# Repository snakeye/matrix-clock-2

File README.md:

# LED Matrix Clock

These clock are build using ESP8266 module ESP-12. Arduino IDE was used for the firmware development and upload.

## Features

* Built on ESP8266 WiFi module
* Time updates via NTP protocol
* Automatic time zone support
* Timekeeping without Internet connection (DS3231 chip)
* Brightness auto adjust

## Dependencies

* WiFi Manager - [https://github.com/tzapu/WiFiManager](https://github.com/tzapu/WiFiManager)
* Time library - [https://github.com/PaulStoffregen/Time](https://github.com/PaulStoffregen/Time)
* Time zone library - [https://github.com/JChristensen/Timezone](https://github.com/JChristensen/Timezone)
* NTP Client - [https://github.com/gmag11/NtpClient](https://github.com/gmag11/NtpClient)
* RTC library - [https://github.com/Makuna/Rtc](https://github.com/Makuna/Rtc)
* MAX7219 library - [https://github.com/snakeye/MAX7219_Display](https://github.com/snakeye/MAX7219_Display)

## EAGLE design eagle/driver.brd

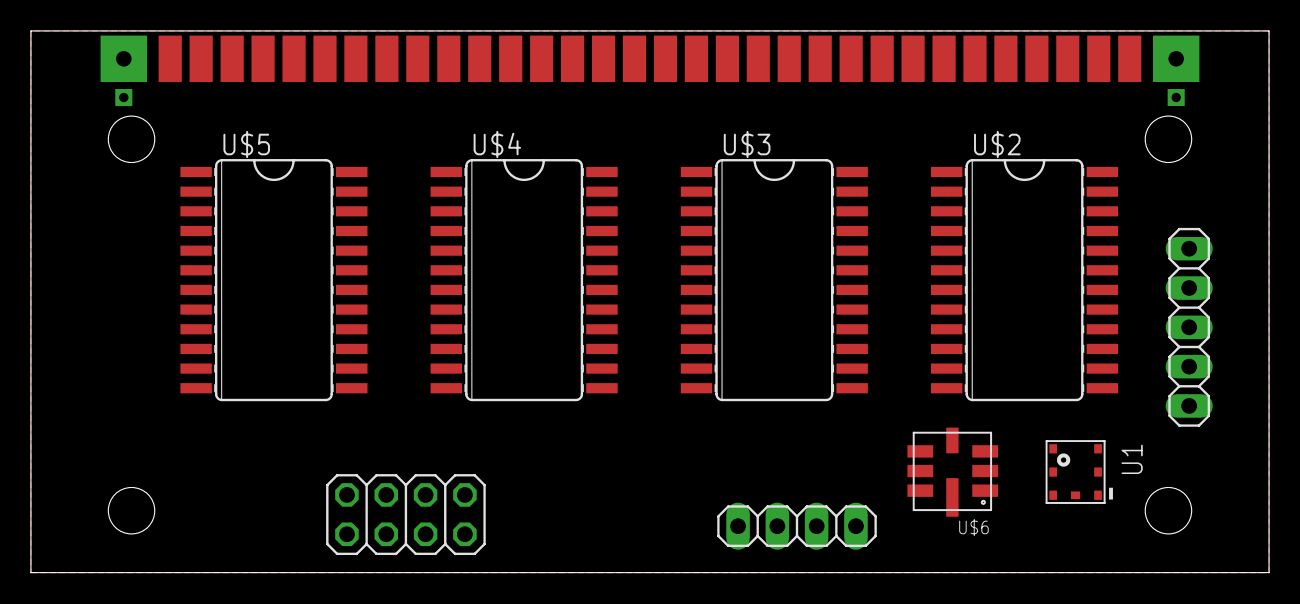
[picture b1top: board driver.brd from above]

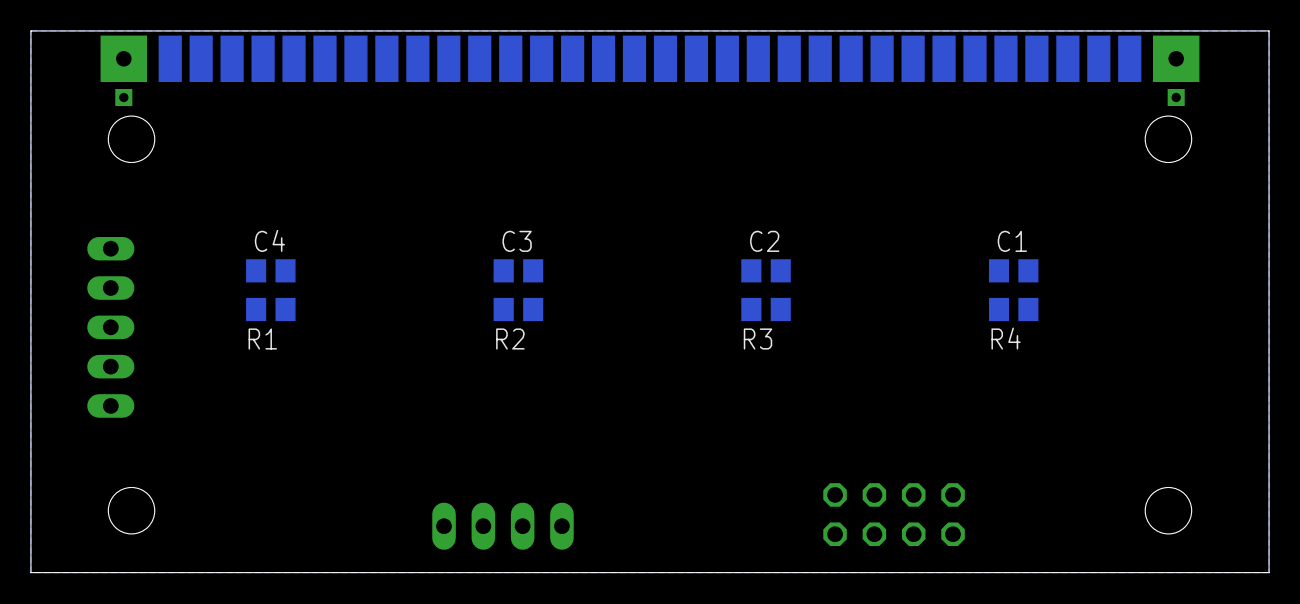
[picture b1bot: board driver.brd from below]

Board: 2 copper layers, 80.0 x 35.0 mm, 18 parts (8 on the bottom side), 79 nets, no tracks yet.

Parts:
C1, C2, C3, C4: C0805
JP1: PROG; 2X04
JP2: DISPLAY; 1X05
JP3: I2C; 1X04
R1, R2, R3, R4: R0805
U1: BMP180
U$1: ANGLE_BOARD_CONNECTORTWO_SIDED; TWO_SIDED
U$2, U$3, U$4, U$5: MAX7219CWG; SO24L
U$6: BMP085

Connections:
+3V3: JP1.7, JP3.3, U1.2, U1.3, U$6.3, U$6.4
+5V: C1.1, C2.1, C3.1, C4.1, JP2.5, R1.1, R2.1, R3.1, R4.1, U$2.19, U$3.19, U$4.19, U$5.19
DSP_CLK: JP2.2, U$2.13, U$3.13, U$4.13, U$5.13
DSP_CS: JP2.3, U$2.12, U$3.12, U$4.12, U$5.12
DSP_DIN: JP2.1, U$2.1
GND: C1.2, C2.2, C3.2, C4.2, JP1.2, JP2.4, JP3.4, U1.7, U$1.GND@1, U$1.GND@2, U$1.GND@3, U$1.GND@4, U$2.4, U$2.9, U$3.4, U$3.9, U$4.4, U$4.9, U$5.4, U$5.9, U$6.1
M1C1: U$1.P$64, U$2.2
M1C2: U$1.P$63, U$2.11
M1C3: U$1.P$62, U$2.6
M1C4: U$1.P$61, U$2.7
M1C5: U$1.P$60, U$2.3
M1C6: U$1.P$59, U$2.10
M1C7: U$1.P$58, U$2.5
M1C8: U$1.P$57, U$2.8
M1R1: U$1.P$1, U$2.14
M1R2: U$1.P$2, U$2.16
M1R3: U$1.P$3, U$2.20
M1R4: U$1.P$4, U$2.23
M1R5: U$1.P$5, U$2.21
M1R6: U$1.P$6, U$2.15
M1R7: U$1.P$7, U$2.17
M1R8: U$1.P$8, U$2.22
M2C1: U$1.P$56, U$3.2
M2C2: U$1.P$55, U$3.11
M2C3: U$1.P$54, U$3.6
M2C4: U$1.P$53, U$3.7
M2C5: U$1.P$52, U$3.3
M2C6: U$1.P$51, U$3.10
M2C7: U$1.P$50, U$3.5
M2C8: U$1.P$49, U$3.8
M2R1: U$1.P$9, U$3.14
M2R2: U$1.P$10, U$3.16
M2R3: U$1.P$11, U$3.20
M2R4: U$1.P$12, U$3.23
M2R5: U$1.P$13, U$3.21
M2R6: U$1.P$14, U$3.15
M2R7: U$1.P$15, U$3.17
M2R8: U$1.P$16, U$3.22
M3C1: U$1.P$48, U$4.2
M3C2: U$1.P$47, U$4.11
M3C3: U$1.P$46, U$4.6
M3C4: U$1.P$45, U$4.7
M3C5: U$1.P$44, U$4.3
M3C6: U$1.P$43, U$4.10
M3C7: U$1.P$42, U$4.5
M3C8: U$1.P$41, U$4.8
M3R1: U$1.P$17, U$4.14
M3R2: U$1.P$18, U$4.16
M3R3: U$1.P$19, U$4.20
M3R4: U$1.P$20, U$4.23
M3R5: U$1.P$21, U$4.21
M3R6: U$1.P$22, U$4.15
M3R7: U$1.P$23, U$4.17
M3R8: U$1.P$24, U$4.22
M4C1: U$1.P$40, U$5.2
M4C2: U$1.P$39, U$5.11
M4C3: U$1.P$38, U$5.6
M4C4: U$1.P$37, U$5.7
M4C5: U$1.P$36, U$5.3
M4C6: U$1.P$35, U$5.10
M4C7: U$1.P$34, U$5.5
M4C8: U$1.P$33, U$5.8
M4R1: U$1.P$25, U$5.14
M4R2: U$1.P$26, U$5.16
M4R3: U$1.P$27, U$5.20
M4R4: U$1.P$28, U$5.23
M4R5: U$1.P$29, U$5.21
M4R6: U$1.P$30, U$5.15
M4R7: U$1.P$31, U$5.17
M4R8: U$1.P$32, U$5.22
unnamed: R1.2, U$2.18
unnamed: U$2.24, U$3.1
unnamed: R2.2, U$3.18
unnamed: U$3.24, U$4.1
unnamed: R3.2, U$4.18
unnamed: U$4.24, U$5.1
unnamed: R4.2, U$5.18
SCL: JP3.1, U1.5, U$6.6
SDA: JP3.2, U1.6, U$6.7

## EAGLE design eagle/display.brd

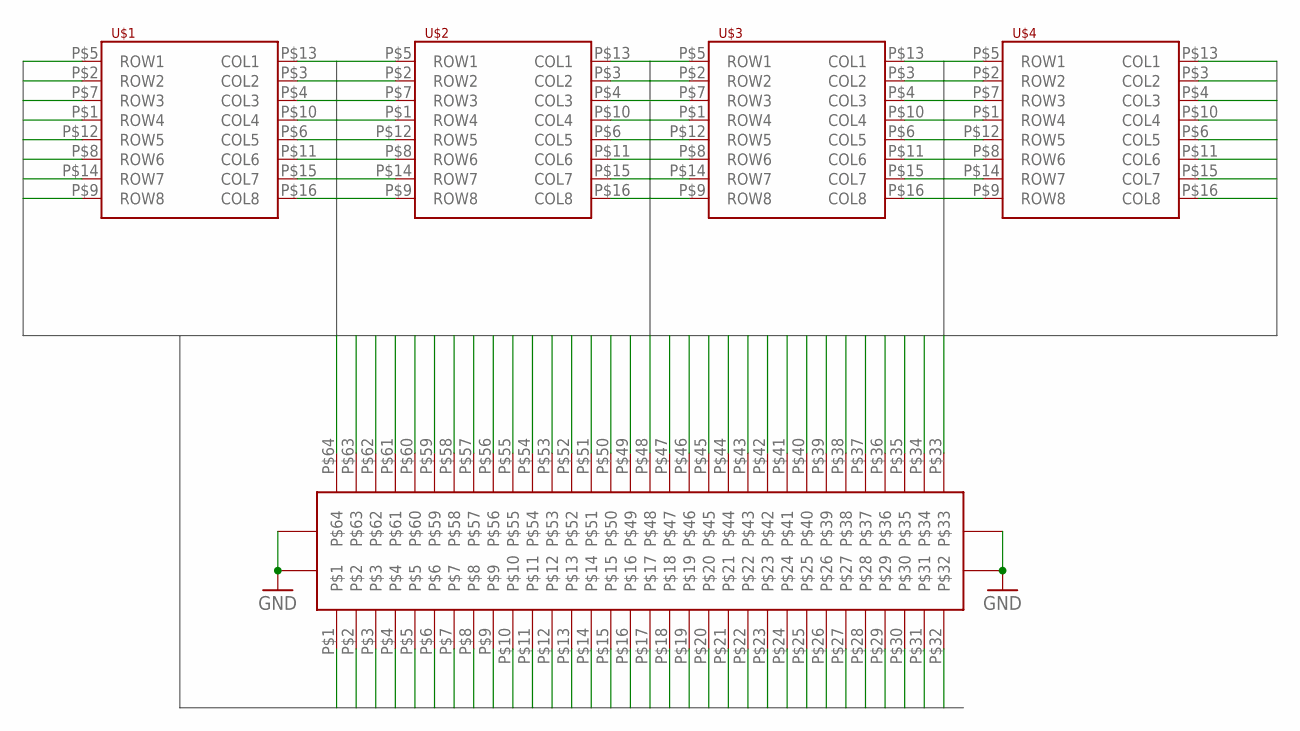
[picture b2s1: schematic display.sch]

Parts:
U$1, U$2, U$3, U$4: LED_8X8_MATRIX07088BH; MATRIX_8X8_20MM
U$5: ANGLE_BOARD_CONNECTORONE_SIDED; ONE_SIDED

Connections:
GND: U$5.GND@1 (GND), U$5.GND@2 (GND), U$5.GND@3 (GND), U$5.GND@4 (GND)
M1C1: U$1.P$13 (COL1), U$5.P$64
M1C2: U$1.P$3 (COL2), U$5.P$63
M1C3: U$1.P$4 (COL3), U$5.P$62
M1C4: U$1.P$10 (COL4), U$5.P$61
M1C5: U$1.P$6 (COL5), U$5.P$60
M1C6: U$1.P$11 (COL6), U$5.P$59
M1C7: U$1.P$15 (COL7), U$5.P$58
M1C8: U$1.P$16 (COL8), U$5.P$57
M1R1: U$1.P$5 (ROW1), U$5.P$1
M1R2: U$1.P$2 (ROW2), U$5.P$2
M1R3: U$1.P$7 (ROW3), U$5.P$3
M1R4: U$1.P$1 (ROW4), U$5.P$4
M1R5: U$1.P$12 (ROW5), U$5.P$5
M1R6: U$1.P$8 (ROW6), U$5.P$6
M1R7: U$1.P$14 (ROW7), U$5.P$7
M1R8: U$1.P$9 (ROW8), U$5.P$8
M2C1: U$2.P$13 (COL1), U$5.P$56
M2C2: U$2.P$3 (COL2), U$5.P$55
M2C3: U$2.P$4 (COL3), U$5.P$54
M2C4: U$2.P$10 (COL4), U$5.P$53
M2C5: U$2.P$6 (COL5), U$5.P$52
M2C6: U$2.P$11 (COL6), U$5.P$51
M2C7: U$2.P$15 (COL7), U$5.P$50
M2C8: U$2.P$16 (COL8), U$5.P$49
M2R1: U$2.P$5 (ROW1), U$5.P$9
M2R2: U$2.P$2 (ROW2), U$5.P$10
M2R3: U$2.P$7 (ROW3), U$5.P$11
M2R4: U$2.P$1 (ROW4), U$5.P$12
M2R5: U$2.P$12 (ROW5), U$5.P$13
M2R6: U$2.P$8 (ROW6), U$5.P$14
M2R7: U$2.P$14 (ROW7), U$5.P$15
M2R8: U$2.P$9 (ROW8), U$5.P$16
M3C1: U$3.P$13 (COL1), U$5.P$48
M3C2: U$3.P$3 (COL2), U$5.P$47
M3C3: U$3.P$4 (COL3), U$5.P$46
M3C4: U$3.P$10 (COL4), U$5.P$45
M3C5: U$3.P$6 (COL5), U$5.P$44
M3C6: U$3.P$11 (COL6), U$5.P$43
M3C7: U$3.P$15 (COL7), U$5.P$42
M3C8: U$3.P$16 (COL8), U$5.P$41
M3R1: U$3.P$5 (ROW1), U$5.P$17
M3R2: U$3.P$2 (ROW2), U$5.P$18
M3R3: U$3.P$7 (ROW3), U$5.P$19
M3R4: U$3.P$1 (ROW4), U$5.P$20
M3R5: U$3.P$12 (ROW5), U$5.P$21
M3R6: U$3.P$8 (ROW6), U$5.P$22
M3R7: U$3.P$14 (ROW7), U$5.P$23
M3R8: U$3.P$9 (ROW8), U$5.P$24
M4C1: U$4.P$13 (COL1), U$5.P$40
M4C2: U$4.P$3 (COL2), U$5.P$39
M4C3: U$4.P$4 (COL3), U$5.P$38
M4C4: U$4.P$10 (COL4), U$5.P$37
M4C5: U$4.P$6 (COL5), U$5.P$36
M4C6: U$4.P$11 (COL6), U$5.P$35
M4C7: U$4.P$15 (COL7), U$5.P$34
M4C8: U$4.P$16 (COL8), U$5.P$33
M4R1: U$4.P$5 (ROW1), U$5.P$25
M4R2: U$4.P$2 (ROW2), U$5.P$26
M4R3: U$4.P$7 (ROW3), U$5.P$27
M4R4: U$4.P$1 (ROW4), U$5.P$28
M4R5: U$4.P$12 (ROW5), U$5.P$29
M4R6: U$4.P$8 (ROW6), U$5.P$30
M4R7: U$4.P$14 (ROW7), U$5.P$31
M4R8: U$4.P$9 (ROW8), U$5.P$32

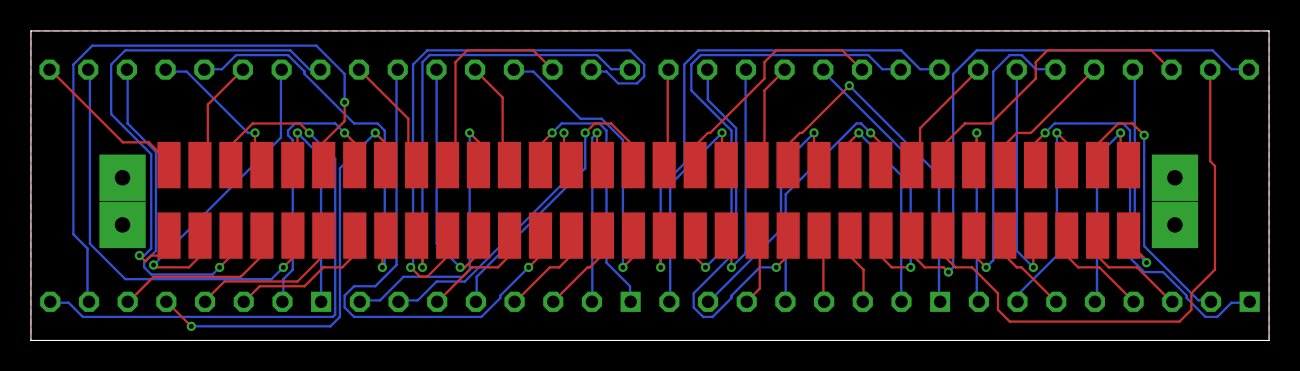
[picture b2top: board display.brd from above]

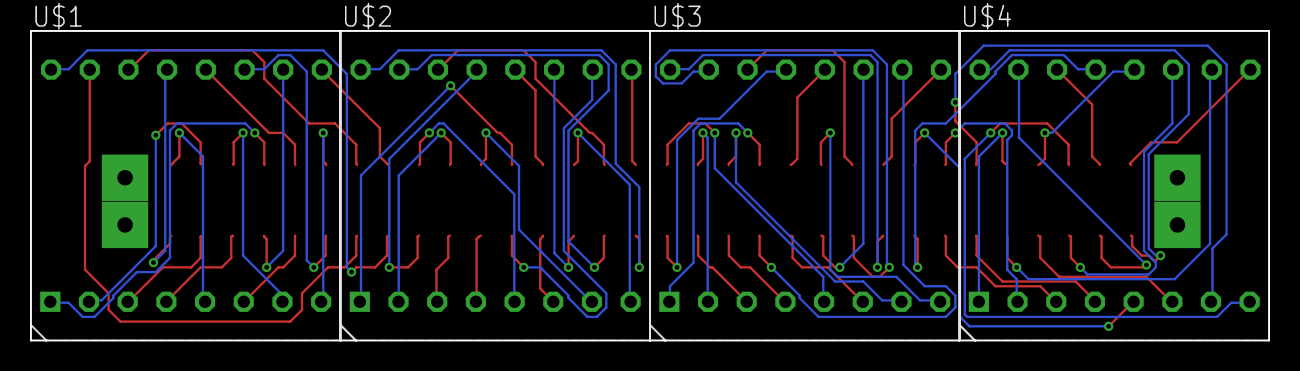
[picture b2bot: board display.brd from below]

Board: 2 copper layers, 80.0 x 20.0 mm, 5 parts (4 on the bottom side), 65 nets.

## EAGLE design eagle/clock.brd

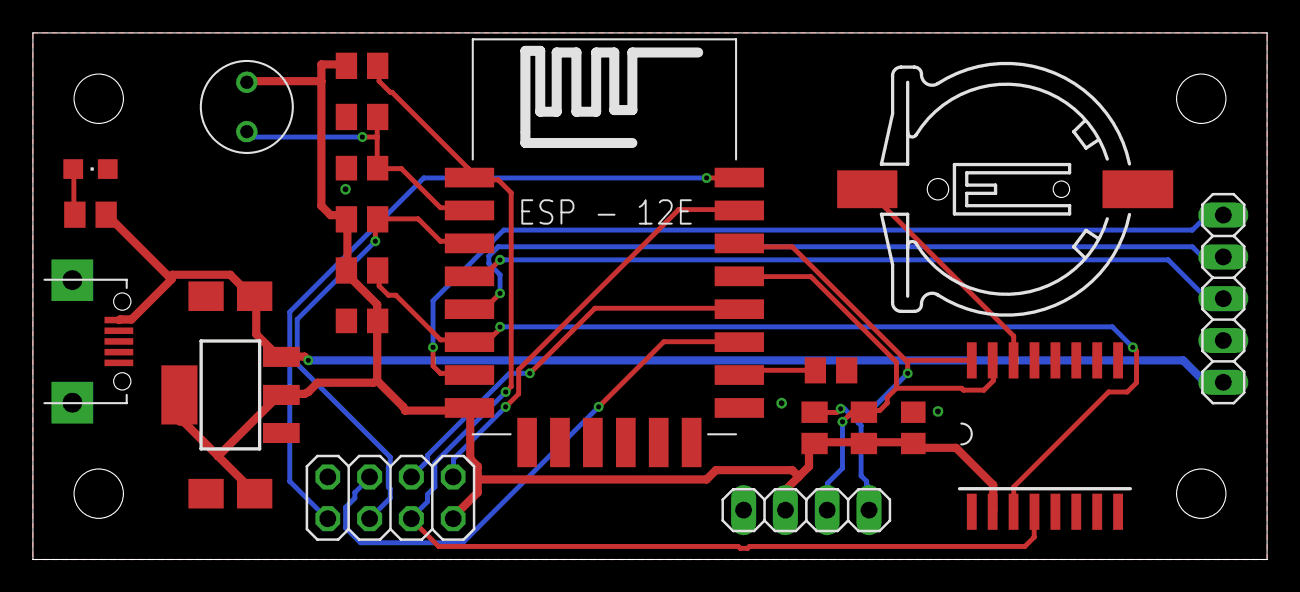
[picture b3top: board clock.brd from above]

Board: 2 copper layers, 75.0 x 32.0 mm, 23 parts (0 on the bottom side), 19 nets.

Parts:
C1, C4, C5: 100u; C0805
C2: 10mF; A/3216-18W
C3: 100mF; A/3216-18W
G1: CH291-1220LF
IC1: LM1117MPX-3.3; SOT223
IC2: DS3231; SOIC-16W
JP1: PROG; 2X04
JP2: DISPLAY; 1X05
JP3: I2C; 1X04
LED1: G; CHIPLED_0805
R1, R2, R4, R5, R6, R7: 4.7k; M0805
R3: 68k; M0805
R8: 330; M0805
U2: ESP12E; ESP12E-SMD
U$1: MICRO-USB
U$2: GL5537; GL55

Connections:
+3V3: C3.+, C4.1, C5.1, IC1.2, IC1.TAB, IC2.2, JP1.7, JP3.3, R1.2, R2.2, R4.2, R5.2, R7.2, U2.VCC, U$2.P$2
+5V: C2.+, IC1.3, JP2.5, R8.2, U$1.1
CH_PD: JP1.3, R5.1, U2.CH_PD
DSP_CLK: JP2.2, U2.GPIO14
DSP_CS: JP2.3, U2.GPIO16
DSP_DIN: JP2.1, U2.GPIO13
GND: C1.2, C2.-, C3.-, C4.2, C5.2, G1.-, IC1.1, IC2.5, IC2.6, IC2.7, IC2.8, IC2.9, IC2.10, IC2.11, IC2.12, IC2.13, JP1.2, JP2.4, JP3.4, LED1.C, R3.1, R6.2, U2.GND, U$1.5, U$1.GND1, U$1.GND2
GPIO0: JP1.6, U2.GPIO0
GPIO2: JP1.4, U2.GPIO2
GPIO15: R6.1, U2.GPIO15
LIGHT_SENSOR: C1.1, R3.2, U2.ADC, U$2.P$1
unnamed: LED1.A, R8.1
unnamed: G1.+, IC2.14
RESET: IC2.4, JP1.5, R4.1, U2.RESET
RX: JP1.8, U2.RXD0
SCL: IC2.16, JP3.1, R2.1, U2.GPIO5
SDA: IC2.15, JP3.2, R1.1, U2.GPIO4
TIMER_INT: IC2.3, R7.1, U2.GPIO12
TX: JP1.1, U2.TXD0

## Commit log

2018-04-26 initial schematic files
2018-04-29 First version of board design
2018-04-29 schematic image
2018-04-29 board updated
2018-05-01 final design
2018-05-10 display and driver boards
2018-05-12 max7219 connection
2018-05-31 added sources for arduino
2018-06-10 proportional thin font
2018-06-10 small refactoring
2018-06-11 NTP clock
2018-06-11 Async NTP
2018-06-12 moved display to separate library
2018-07-15 firmware initial commit
2018-09-30 added arduino dir
2018-10-01 Added libraries
2018-10-01 Added .gitignore for arduino project
2018-10-02 Added WiFi connection
2018-10-03 Time from NTP
2018-10-03 connected led matrix display
2018-10-03 Clock + NTP + Brightness + blinking dots
2018-10-03 Correct brightness calculation
2018-10-03 Removed leading zero from hours
2018-10-03 Onboard led on when no wifi connection
2018-10-05 OTA updates
2018-10-05 Small code cleanup
2018-10-12 Set initial brightness; disable led
2018-10-30 Removed unused variables
2021-02-22 ESPHome
2021-02-22 Time display
2021-02-23 Ambient light sensor
2021-02-25 DS3231 handling
2021-02-25 Removed filter
2021-02-25 Added enclosure model
2021-02-25 ESPHome version
2021-04-15 dependency update
2023-12-15 Add renovate.json
2024-03-25 Updated version
2024-03-25 Bump cryptography from 42.0.2 to 42.0.4 in /firmware
    Bumps [cryptography](https://github.com/pyca/cryptography) from 42.0.2 to 42.0.4.
    - [Changelog](https://github.com/pyca/cryptography/blob/main/CHANGELOG.rst)
    - [Commits](https://github.com/pyca/cryptography/compare/42.0.2...42.0.4)
    ---
    updated-dependencies:
    - dependency-name: cryptography
2024-03-25 Bump cryptography from 42.0.2 to 42.0.4 in /firmware (#4)
    Bumps [cryptography](https://github.com/pyca/cryptography) from 42.0.2 to 42.0.4.
    - [Changelog](https://github.com/pyca/cryptography/blob/main/CHANGELOG.rst)
    - [Commits](https://github.com/pyca/cryptography/compare/42.0.2...42.0.4)
    ---
    updated-dependencies:
    - dependency-name: cryptography
2024-04-03 Bump pillow from 10.2.0 to 10.3.0 in /firmware
    Bumps [pillow](https://github.com/python-pillow/Pillow) from 10.2.0 to 10.3.0.
    - [Release notes](https://github.com/python-pillow/Pillow/releases)
    - [Changelog](https://github.com/python-pillow/Pillow/blob/main/CHANGES.rst)
    - [Commits](https://github.com/python-pillow/Pillow/compare/10.2.0...10.3.0)
    ---
    updated-dependencies:
2024-04-12 Bump idna from 3.6 to 3.7 in /firmware
    Bumps [idna](https://github.com/kjd/idna) from 3.6 to 3.7.
    - [Release notes](https://github.com/kjd/idna/releases)
    - [Changelog](https://github.com/kjd/idna/blob/master/HISTORY.rst)
    - [Commits](https://github.com/kjd/idna/compare/v3.6...v3.7)
    ---
    updated-dependencies:
2024-05-21 --- updated-dependencies: - dependency-name: requests dependency-type: indirect ...
2024-06-17 Bump urllib3 from 2.2.1 to 2.2.2 in /firmware
    Bumps [urllib3](https://github.com/urllib3/urllib3) from 2.2.1 to 2.2.2.
    - [Release notes](https://github.com/urllib3/urllib3/releases)
    - [Changelog](https://github.com/urllib3/urllib3/blob/main/CHANGES.rst)
    - [Commits](https://github.com/urllib3/urllib3/compare/2.2.1...2.2.2)
    ---
    updated-dependencies:
